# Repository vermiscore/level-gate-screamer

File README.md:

# level-gate-screamer
Tube Screamer-style overdrive with a level gate: attenuates below threshold, boosts above

> [!WARNING]
> **v1: J2/J3 footprints are rotated 180°.**
> Fix with jumpers on the bottom side:
> - J2: 1–6, 2–5
> - J3: 1–6, 4–2
>
> Next revision: rotate J2/J3 so the big protrusion faces the board edge.
>
> **Output level:** up to ~9 Vpp (rail-to-rail op-amps on 9 V).
> Check the input range of the next device before connecting.
> Tested OK with a Neural DSP Nano Cortex.

## Files
- `kicad_files/` — KiCad project
- `fabrication/` — Gerber, BOM, CPL for JLCPCB
- `hand_soldered_parts/` — parts not assembled by JLCPCB
- `simulation/` — ngspice netlist

## Images

### Finished PCB

### PCB just arrived

### PCB layout (KiCad)

### Schematic

Labeled as "OTA boost", but this isn't an OTA.
### Level gate concept

### Simulation: input above threshold (amplified)

### Simulation: input below threshold (attenuated)

## Impressions
- Sounds great
- Easy to play
- The gate works as intended

## References
- [UC3Music/IceScreamer](https://github.com/UC3Music/IceScreamer) — base Tube Screamer design and footprints
- [ElectroSmash Archive: Tube Screamer Analysis](https://electrosmash.mas-effects.com/tube-screamer-analysis)
- [ElectroSmash Archive: MXR MicroAmp Analysis](https://electrosmash.mas-effects.com/mxr-microamp) — boost stage
- [PCB Guitar Mania: No-Noise Gate building docs (PDF)](https://pcbguitarmania.com/wp-content/uploads/2018/07/No-Noise-Gate-1.2v-Building-Docs.pdf) — noise gate
- [Elliott Sound Products: VCA Techniques Investigated](https://sound-au.com/articles/vca-techniques.html) — JFET VCA (Figure B)
- Boss NS-2 — gate idea: detect on the dry signal, mute after the gain stage

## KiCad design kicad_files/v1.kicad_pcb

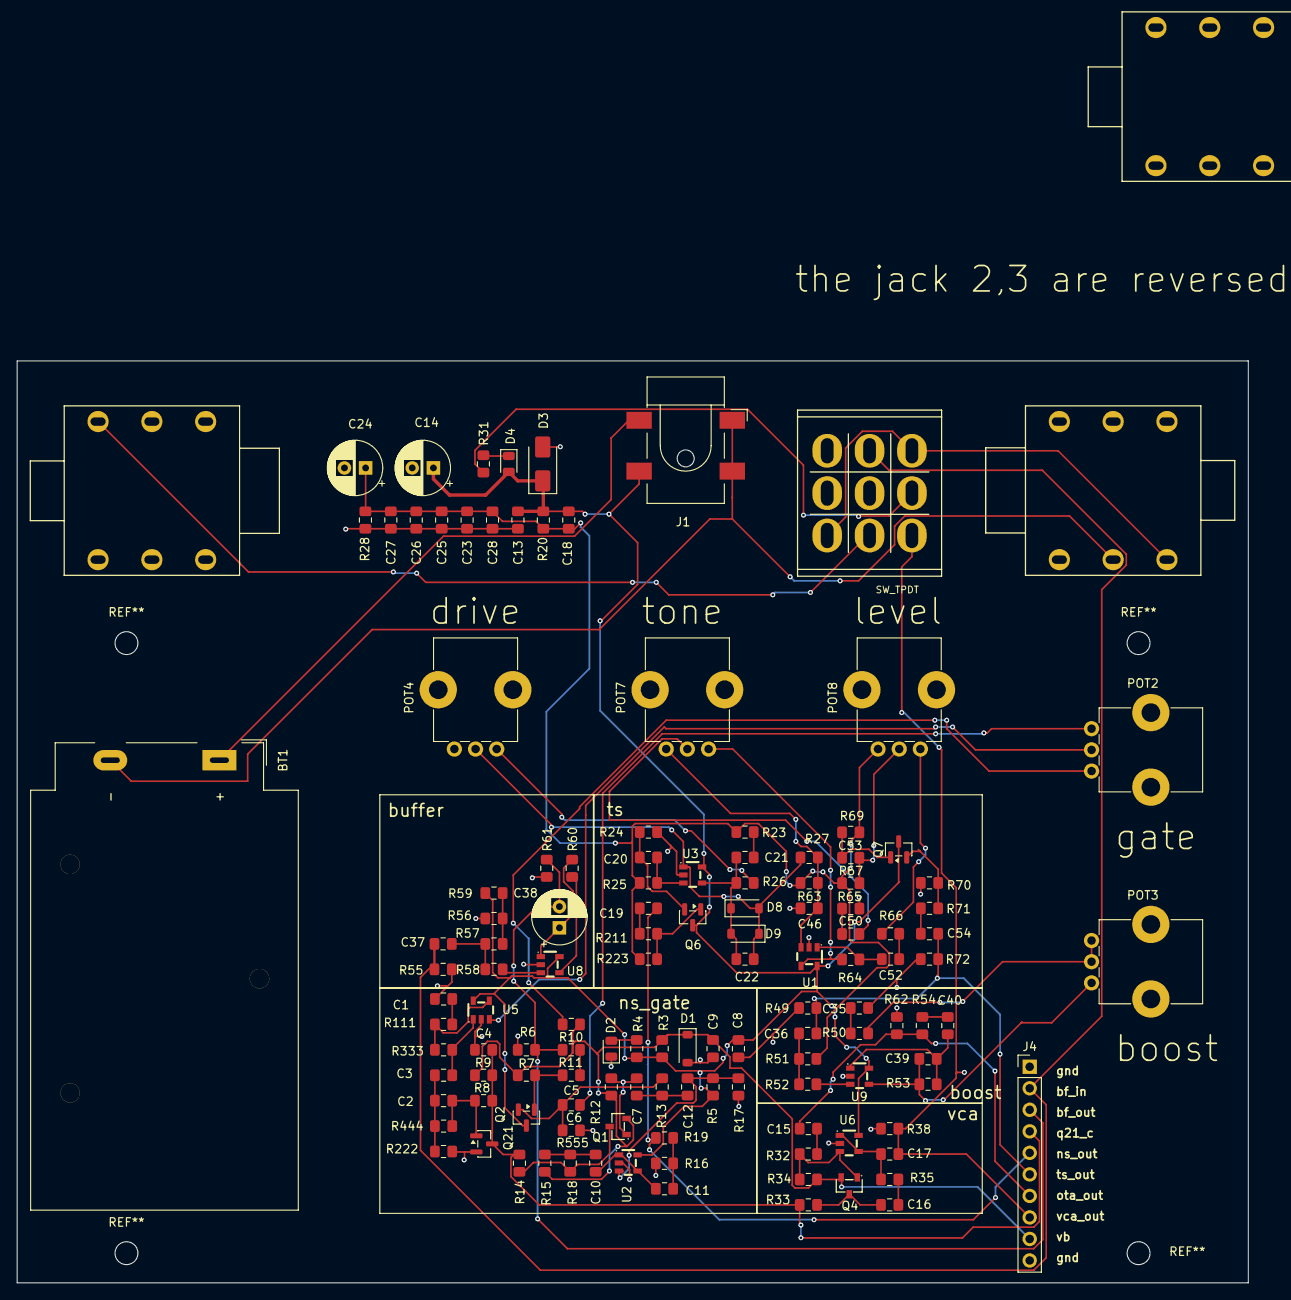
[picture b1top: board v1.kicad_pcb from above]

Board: 2 copper layers, 145.3 x 108.8 mm, 130 parts (0 on the bottom side), 72 nets.

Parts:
BT1: Battery_Cell; BatteryHolder_MPD_BA9VPC_1xPP3
C1: 2.2u; C_0805_2012Metric_Pad1.15x1.40mm_HandSolder
C2, C5, C6, C12: 10n; C_0805_2012Metric_Pad1.15x1.40mm_HandSolder
C3, C10: 47n; C_0805_2012Metric_Pad1.15x1.40mm_HandSolder
C4, C16, C17, C20: 1u; C_0805_2012Metric_Pad1.15x1.40mm_HandSolder
C7, C8, C9, C11, C15: 10u; C_0805_2012Metric_Pad1.15x1.40mm_HandSolder
C13, C18, C23, C25, C26, C27, C28, C53: 100nF; C_0805_2012Metric_Pad1.15x1.40mm_HandSolder
C14, C24: 220uF; CP_Radial_D6.3mm_P2.50mm
C19: 22n; C_0805_2012Metric_Pad1.15x1.40mm_HandSolder
C21: 47nF; C_0805_2012Metric_Pad1.15x1.40mm_HandSolder
C22, C39: 47p; C_0805_2012Metric_Pad1.15x1.40mm_HandSolder
C35: 4.7u; C_0805_2012Metric_Pad1.15x1.40mm_HandSolder
C36: 0.1u; C_0805_2012Metric_Pad1.15x1.40mm_HandSolder
C37: 100n; C_0805_2012Metric_Pad1.15x1.40mm_HandSolder
C38: 100u; CP_Radial_D6.3mm_P2.50mm
C40: 15u; C_0805_2012Metric_Pad1.15x1.40mm_HandSolder
C46, C50: 220nF; C_0805_2012Metric_Pad1.15x1.40mm_HandSolder
C52: 1uF; C_0805_2012Metric_Pad1.15x1.40mm_HandSolder
C54: 10uF; C_0805_2012Metric_Pad1.15x1.40mm_HandSolder
D1: 5.1v; D_SOD-123
D2, D4: LED; LED_0805_2012Metric
D3: 1N4001; D_SMA
D8, D9: 1N4148; D_SOD-123
J1: Barrel_Jack_Switch; BarrelJack_CLIFF_FC681465S_SMT_Horizontal
J2, J2#2, J3: NMJ6HFD2; IceJACK
J4: Conn_01x10_Pin; PinHeader_1x10_P2.54mm_Vertical
POT2, POT3: log 500K; Potentiometer_Bourns_PTV09A-1_Single_Vertical
POT4: log 500k; Potentiometer_Bourns_PTV09A-1_Single_Vertical
POT7: lin 20k; Potentiometer_Bourns_PTV09A-1_Single_Vertical
POT8: log 100K; Potentiometer_Bourns_PTV09A-1_Single_Vertical
Q1, Q4: Q_NJFET_GDS; SOT-23-3_L2.9-W1.3-P1.90-LS2.4-BR
Q2, Q6, Q7, Q21: NPN_BC847B; SOT-23
R3, R13, R222, R555: 22k; R_0805_2012Metric_Pad1.15x1.40mm_HandSolder
R4: 3.3k; R_0805_2012Metric_Pad1.15x1.40mm_HandSolder
R5, R8, R12, R17, R18, R34, R333: 1M; R_0805_2012Metric_Pad1.15x1.40mm_HandSolder
R6, R55, R57: 2.2M; R_0805_2012Metric_Pad1.15x1.40mm_HandSolder
R7: 470k; R_0805_2012Metric_Pad1.15x1.40mm_HandSolder
R9: 150k; R_0805_2012Metric_Pad1.15x1.40mm_HandSolder
R10: 1k; R_0805_2012Metric_Pad1.15x1.40mm_HandSolder
R11, R16, R38, R58, R62: 10k; R_0805_2012Metric_Pad1.15x1.40mm_HandSolder
R14: 1.8k; R_0805_2012Metric_Pad1.15x1.40mm_HandSolder
R15, R32, R56, R59, R444: 100k; R_0805_2012Metric_Pad1.15x1.40mm_HandSolder
R19, R61: 100; R_0805_2012Metric_Pad1.15x1.40mm_HandSolder
R20, R24, R25, R28, R63, R67, R70, R72: 10K; R_0805_2012Metric_Pad1.15x1.40mm_HandSolder
R23, R111: 4.7k; R_0805_2012Metric_Pad1.15x1.40mm_HandSolder
R26: 47k; R_0805_2012Metric_Pad1.15x1.40mm_HandSolder
R27, R52, R64, R66, R211: 1K; R_0805_2012Metric_Pad1.15x1.40mm_HandSolder
R31: 2.2k; R_0805_2012Metric_Pad1.15x1.40mm_HandSolder
R33: 9.53k; R_0805_2012Metric_Pad1.15x1.40mm_HandSolder
R35: 200k; R_0805_2012Metric_Pad1.15x1.40mm_HandSolder
R49: 22M; R_0805_2012Metric_Pad1.15x1.40mm_HandSolder
R50: 2.7k; R_0805_2012Metric_Pad1.15x1.40mm_HandSolder
R51: 10M; R_0805_2012Metric_Pad1.15x1.40mm_HandSolder
R53: 56k; R_0805_2012Metric_Pad1.15x1.40mm_HandSolder
R54: 470; R_0805_2012Metric_Pad1.15x1.40mm_HandSolder
R60: 10; R_0805_2012Metric_Pad1.15x1.40mm_HandSolder
R65: 220R; R_0805_2012Metric_Pad1.15x1.40mm_HandSolder
R69, R223: 470K; R_0805_2012Metric_Pad1.15x1.40mm_HandSolder
R71: 100R; R_0805_2012Metric_Pad1.15x1.40mm_HandSolder
SW1: SW_TPDT; IceStomp_Switch_3PDT
U1, U2, U3, U5, U6, U8, U9: LM7301; SOT-23-5_L2.9-W1.6-P0.95-LS2.8-BL

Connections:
+4.5V: C18.2, C23.1, C24.1, C25.1, C26.1, C27.1, C28.1, POT8.3, R20.2, R23.1, R25.2, R28.1, R51.1, R63.1, R67.2, R69.2, R223.2
+9V: C8.1, C13.1, C14.1, C18.1, D3.1 (K), D4.2 (A), J1.2, Q2.3 (C), Q6.3 (C), Q7.3 (C), R3.2, R4.2, R5.2, R20.1, R59.2, U1.5 (VDD), U2.5 (VDD), U3.5 (VDD), U5.5 (VDD), U6.5 (VDD), U8.5 (VDD), U9.5 (VDD)
/vb: C9.1, D1.1 (K), J4.9, Q1.2 (S), Q4.2 (S), R3.1, R7.2, R9.2, R10.2, R12.2, R15.1, R34.1
BATT+: BT1.1 (+), J1.3
BATT-: BT1.2 (-), J1.1, J2#2.2
GND: C1.2, C4.2, C8.2, C9.2, C13.2, C14.2, C23.2, C24.2, C25.2, C26.2, C27.2, C28.2, C35.1, C46.1, D1.2 (A), D2.1 (K), D3.2 (A), J2#2.3, J2#2.4, J3.2, J3.3, J4.1, J4.10, Q21.2 (E), R6.2, R16.2, R17.1, R24.2, R28.2, R38.1, R49.1, R55.1, R56.1, R61.1, R62.1, R65.2, R70.2, R72.2, R222.2, R555.2, SW1.22, SW1.31, U1.2 (GND), U2.2 (GND), U3.2 (GND), U5.2 (GND), U6.2 (GND), U8.2 (GND), U9.2 (GND)
JACK_IN: J2#2.1, SW1.11, SW1.33
JACK_OUT: J3.1, SW1.23
LED_CATHODE: D4.1 (K), R31.1
unnamed: C1.1, R111.2
unnamed: C2.2, C3.1, R222.1, R444.2
unnamed: C5.2, R11.2
unnamed: C6.2, POT2.3
unnamed: C10.1, R15.2, R18.2
unnamed: C7.1, C12.1, R13.2
unnamed: C15.2, R32.2
unnamed: C16.1, R35.1
unnamed: C19.1, R211.2
unnamed: C21.2, R23.2
unnamed: C35.2, R50.1
unnamed: C36.1, R51.2, R52.1
unnamed: C37.1, R57.1, R58.1
unnamed: C40.1, R54.1
unnamed: C50.1, POT7.2
unnamed: C50.2, R65.1
unnamed: C52.1, R66.1
unnamed: C54.2, R71.1
unnamed: D2.2 (A), R4.1
unnamed: C22.1, D8.2 (A), D9.1 (K), POT4.2, R27.2, U3.1 (VOUT)
unnamed: C21.1, C22.2, D8.1 (K), D9.2 (A), R26.2, U3.4 (VIN-)
unnamed: POT2.1, R10.1
unnamed: POT3.2, POT3.3, R50.2
unnamed: POT4.1, R26.1
unnamed: POT8.1, R66.2
unnamed: C7.2, Q1.1 (D), R12.1
unnamed: Q1.3 (G), R14.2, R18.1
unnamed: C5.1, Q2.1 (B), R7.1
unnamed: C6.1, Q2.2 (E), R13.1, R555.1
unnamed: Q4.1 (D), R32.1, R34.2, U6.3 (VIN+)
unnamed: C16.2, Q4.3 (G), R33.1
unnamed: Q6.1 (B), R211.1, R223.1
unnamed: C20.2, Q6.2 (E), R24.1
unnamed: C53.1, Q7.1 (B), R69.1
unnamed: Q7.2 (E), R70.1, R71.2
unnamed: C2.1, Q21.1 (B), R8.2, R444.1
unnamed: R31.2, SW1.12
unnamed: R56.2, R57.2, R59.1
unnamed: C46.2, POT7.3, R27.1, R63.2, U1.3 (VIN+)
unnamed: POT7.1, R64.1, U1.4 (VIN-)
unnamed: C52.2, R64.2, U1.1 (VOUT)
unnamed: C12.2, R5.1, R17.2, U2.3 (VIN+)
unnamed: C10.2, C11.1, U2.1 (VOUT), U2.4 (VIN-)
unnamed: C20.1, R25.1, U3.3 (VIN+)
unnamed: POT2.2, U5.3 (VIN+)
unnamed: R111.1, R333.2, U5.4 (VIN-)
unnamed: C3.2, R333.1, U5.1 (VOUT)
unnamed: C17.2, R35.2, U6.1 (VOUT), U6.4 (VIN-)
unnamed: R58.2, U8.3 (VIN+)
unnamed: R60.1, U8.4 (VIN-)
unnamed: C38.1, R60.2, U8.1 (VOUT)
unnamed: R52.2, U9.3 (VIN+)
unnamed: C39.2, POT3.1, R53.1, U9.4 (VIN-)
unnamed: C39.1, C40.2, R53.2, U9.1 (VOUT)
TS_OUT: C36.2, C54.1, J4.6, R49.2, R72.1
bf_in: C37.2, J4.2, R55.2, SW1.21
bf_out: C38.2, J4.3, R6.1, R11.1, R61.2
connected: C53.2, POT8.2, R67.1
ns_out: C19.2, J4.5, R19.1
ns_out2: C11.2, R16.1, R19.2
ota_out: C15.1, J4.7, R54.2, R62.2
q21_c: C4.1, J4.4, Q21.3 (C), R8.1, R9.1, R14.1, R33.2
vca_out: C17.1, J4.8, R38.2, SW1.13

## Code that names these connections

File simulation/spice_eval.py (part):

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

def extract_labeled_nodes(text):
    """Return only user-assigned net labels (bf_in, vca_out, JACK_IN, ...),
    filtering out KiCad's auto-generated node names (Net-_XXX_,
    unconnected-_XXX_, probe_int_XXX) so the user isn't shown internal
    plumbing they never named themselves."""
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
